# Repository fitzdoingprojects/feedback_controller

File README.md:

# feedback_controller
Analog LiPo Charge controller with PWM overide

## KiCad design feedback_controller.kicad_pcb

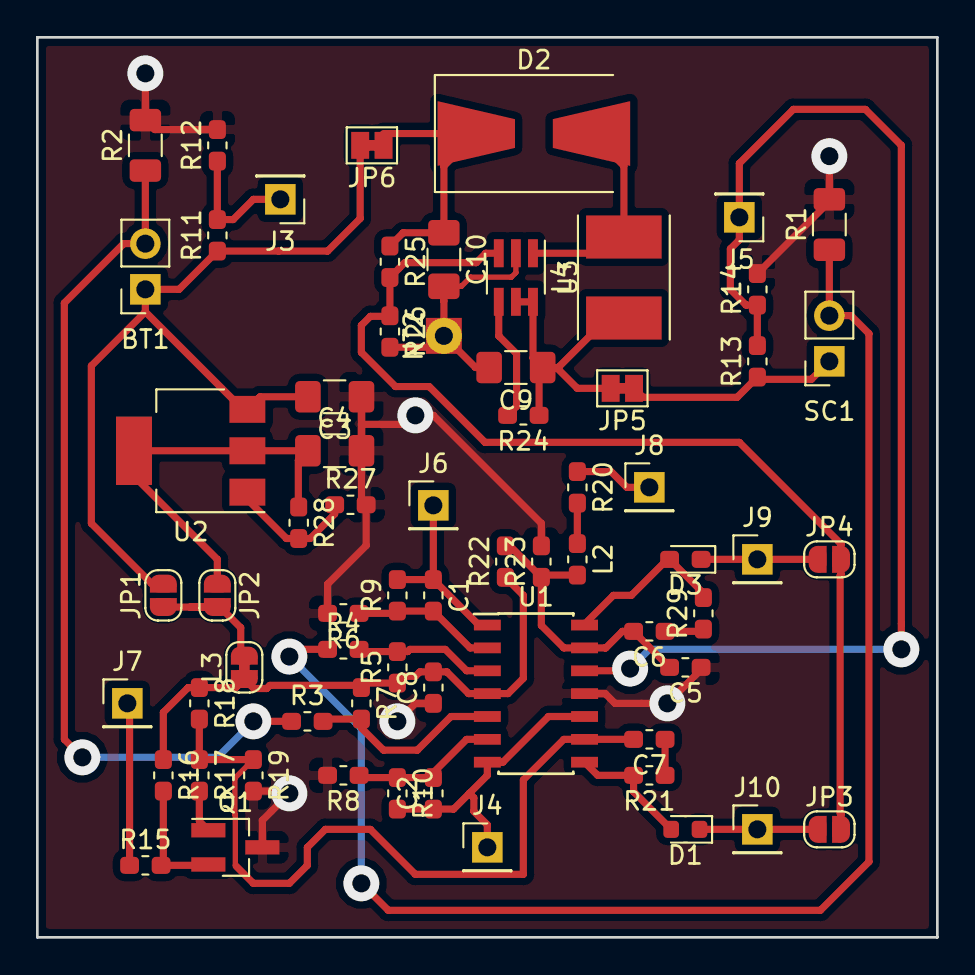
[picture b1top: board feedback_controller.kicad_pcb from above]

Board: 2 copper layers, 50.0 x 50.0 mm, 66 parts (0 on the bottom side), 36 nets.

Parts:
BT1: Battery_Cell; PinSocket_1x02_P2.54mm_Vertical
C1, C2, C5, C8: 0.1uF; C_0603_1608Metric_Pad1.05x0.95mm_HandSolder
C3, C4: 10uF; C_1206_3216Metric_Pad1.42x1.75mm_HandSolder
C6, C7: NC; C_0603_1608Metric_Pad1.05x0.95mm_HandSolder
C9, C10: 22uF; C_1206_3216Metric_Pad1.42x1.75mm_HandSolder
D1: D_Schottky; D_0603_1608Metric_Pad0.88x0.95mm_HandSolder
D2: SS32; D_SMB-SMC_Universal_Handsoldering
D3: D_Schottky; D_0603_1608Metric_Pad1.05x0.95mm_HandSolder
J3: batt_voltage; PinHeader_1x01_P2.54mm_Vertical
J4: batt_current; PinHeader_1x01_P2.54mm_Vertical
J5: v_solar_adc; PinHeader_1x01_P2.54mm_Vertical
J6: solar_current; PinHeader_1x01_P2.54mm_Vertical
J7: TRICKLE_DIS; PinHeader_1x01_P2.54mm_Vertical
J8: PWM_MPPT; PinHeader_1x01_P2.54mm_Vertical
J9: MPPT; PinHeader_1x01_P2.54mm_Vertical
J10: CURRENT_SET; PinHeader_1x01_P2.54mm_Vertical
JP1: BATT+; SolderJumper-2_P1.3mm_Open_RoundedPad1.0x1.5mm
JP2: 2V8; SolderJumper-2_P1.3mm_Open_RoundedPad1.0x1.5mm
JP3, JP4: Jumper_NO_Small; SolderJumper-2_P1.3mm_Open_RoundedPad1.0x1.5mm
JP5, JP6: Jumper_NC_Small; SolderJumper-2_P1.3mm_Bridged_Pad1.0x1.5mm
L2: 100nF; L_0603_1608Metric_Pad1.05x0.95mm_HandSolder
L3: JUMPER; SolderJumper-2_P1.3mm_Bridged_RoundedPad1.0x1.5mm
L4: 4.7uH; L_Taiyo-Yuden_NR-50xx_HandSoldering
NT2: Net-Tie_2; smps_gnd_tie
Q1: AO3400; SOT-23_Handsoldering
R1, R2: 0.1R; R_1206_3216Metric
R3, R4, R6, R8, R12, R15, R19, R23, R27, R28: 1K; R_0603_1608Metric_Pad1.05x0.95mm_HandSolder
R5, R7, R9, R10: 33K; R_0603_1608Metric_Pad1.05x0.95mm_HandSolder
R11, R13, R14, R17: R_Small; R_0603_1608Metric_Pad1.05x0.95mm_HandSolder
R16: 100K; R_0603_1608Metric_Pad1.05x0.95mm_HandSolder
R18, R22: 220K; R_0603_1608Metric_Pad1.05x0.95mm_HandSolder
R20: 100; R_0603_1608Metric_Pad1.05x0.95mm_HandSolder
R21, R29: NC; R_0603_1608Metric_Pad1.05x0.95mm_HandSolder
R24, R25: 20K; R_0603_1608Metric_Pad1.05x0.95mm_HandSolder
R26: 120K; R_0603_1608Metric_Pad1.05x0.95mm_HandSolder
SC1: Solar_Cell; PinSocket_1x02_P2.54mm_Vertical
U1: LMV324; SOIC-14_3.9x8.7mm_P1.27mm
U2: LM317_ADJ; SOT-223-3_TabPin2
U3: SD6201; SOT-23-6_Handsoldering

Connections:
+2V8: C4.1, JP2.1, R28.1, U2.2
+BATT: BT1.1, C3.2, JP1.2, JP6.2, R11.1, U2.3
+VSW: JP5.1, R13.1, SC1.1
/A+: R4.2, R5.2, U1.3
/A-: C1.2, R6.1, R9.1, U1.2
/B+: R3.2, R7.2, U1.5
/B-: C2.2, R8.1, R10.1, U1.6
/BATT_CUR: BT1.2, R2.1, R3.1
/MT_EN: R24.2, U3.4
/MT_FB: JP3.2, JP4.2, R25.2, R26.1, U3.3
/MT_GND: C9.2, C10.2, NT2.1, R26.2, U3.2
/MT_IN: C9.1, JP5.2, L4.1, R24.1, U3.5, U3.6
/MT_OUT: C10.1, D2.1, JP6.1, R25.1
/MT_SW: D2.2, L4.2, U3.1
/SOLAR_CUR: R1.1, R4.1, SC1.2
/V_op: C8.2, L3.1, R5.1, R7.1, R16.1, R18.1, R22.1, U1.4
/batt_current: C2.1, J4.1, R10.2, U1.7, U1.10
/cur_output: D1.2, R21.2, U1.8
/mppt_out: D3.2, R29.2, U1.14
/pwm: L2.1, R20.2
/set_current: C7.2, R17.1, R18.2, R19.1, U1.9
/solar_current: C1.1, J6.1, R9.2, U1.1
/v_mppt_set: C5.2, C6.2, L2.2, R22.2, R23.1, U1.13
/v_solar_adc: J5.1, R13.2, R14.1, U1.12
GND: C3.1, C4.2, C5.1, C8.1, NT2.2, Q1.3, R1.2, R2.2, R6.2, R8.2, R12.2, R14.2, R19.2, R23.2, R27.2, U1.11
unnamed: C6.1, R29.1
unnamed: C7.1, R21.1
unnamed: D1.1, J10.1, JP3.1
unnamed: D3.1, J9.1, JP4.1
unnamed: J3.1, R11.2, R12.1
unnamed: J7.1, R15.1
unnamed: J8.1, R20.1
unnamed: JP1.1, JP2.2, L3.2
unnamed: Q1.1, R17.2
unnamed: Q1.2, R15.2, R16.2
unnamed: R27.1, R28.2, U2.1

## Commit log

2018-08-08 Adds kicad
2018-08-08 adds update script
